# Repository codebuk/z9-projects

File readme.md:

- Note re projhect UUIDs

stored in [project name].kicad_pro

snup ####################
  "sheets": [
    [
      "8d063f79-9282-4820-bcf4-1ff3c006cf08",
      "Root"
    ],

then 'root' schmeatic 
snip ############
(kicad_sch
	(version 20250114)
	(generator "eeschema")
	(generator_version "9.0")
	(uuid "8d063f79-9282-4820-bcf4-1ff3c006cf08")
	(paper "A3")
	(title_block
		(date "2024-05-30")
	)

-- project uuids
old pdm 8d063f79-9282-4820-bcf4-1ff3c006cf08
new pdm b643db5c-578e-4b48-aafc-cc4190db582a

shared 

new 0d832c56-2071-4d02-b574-dc412c8c5a75

8d063f79-9282-4820-bcf4-1ff3c006cf08

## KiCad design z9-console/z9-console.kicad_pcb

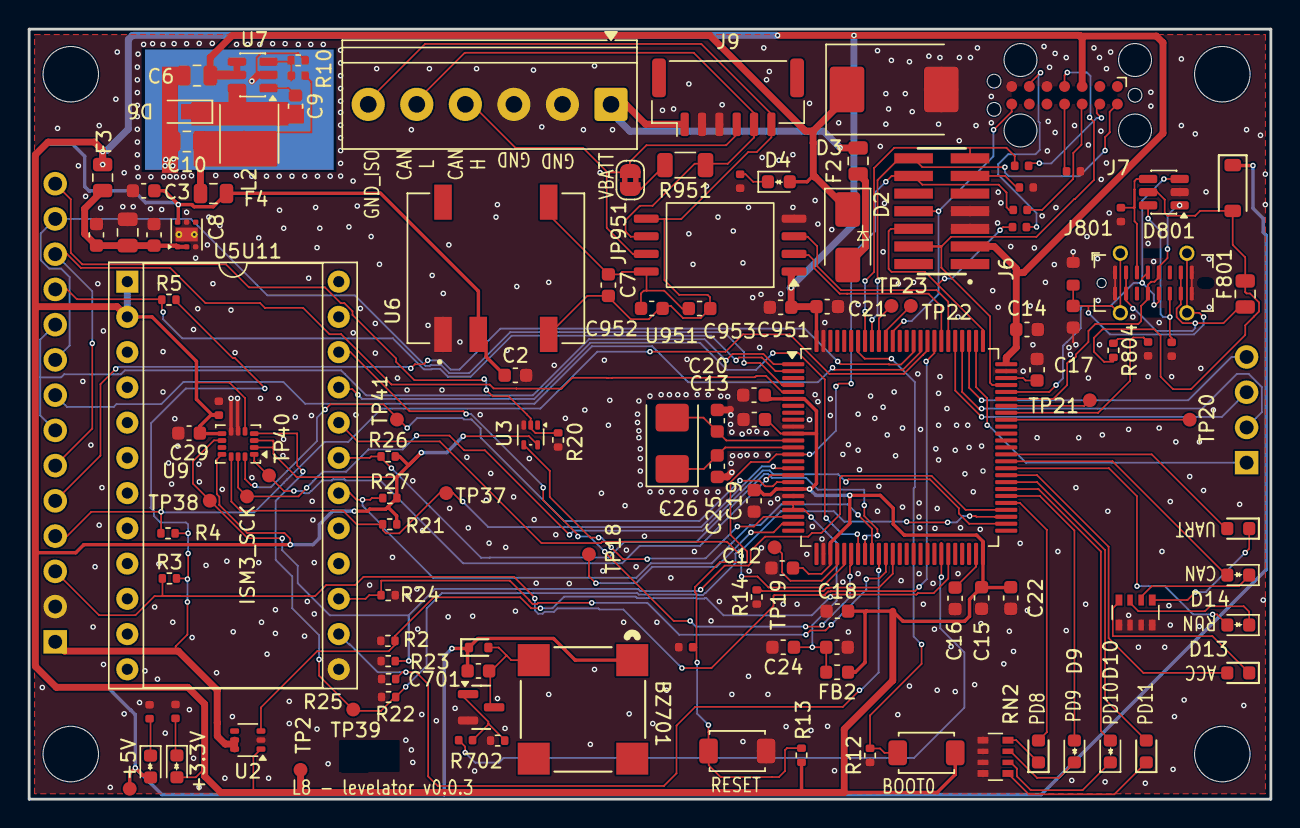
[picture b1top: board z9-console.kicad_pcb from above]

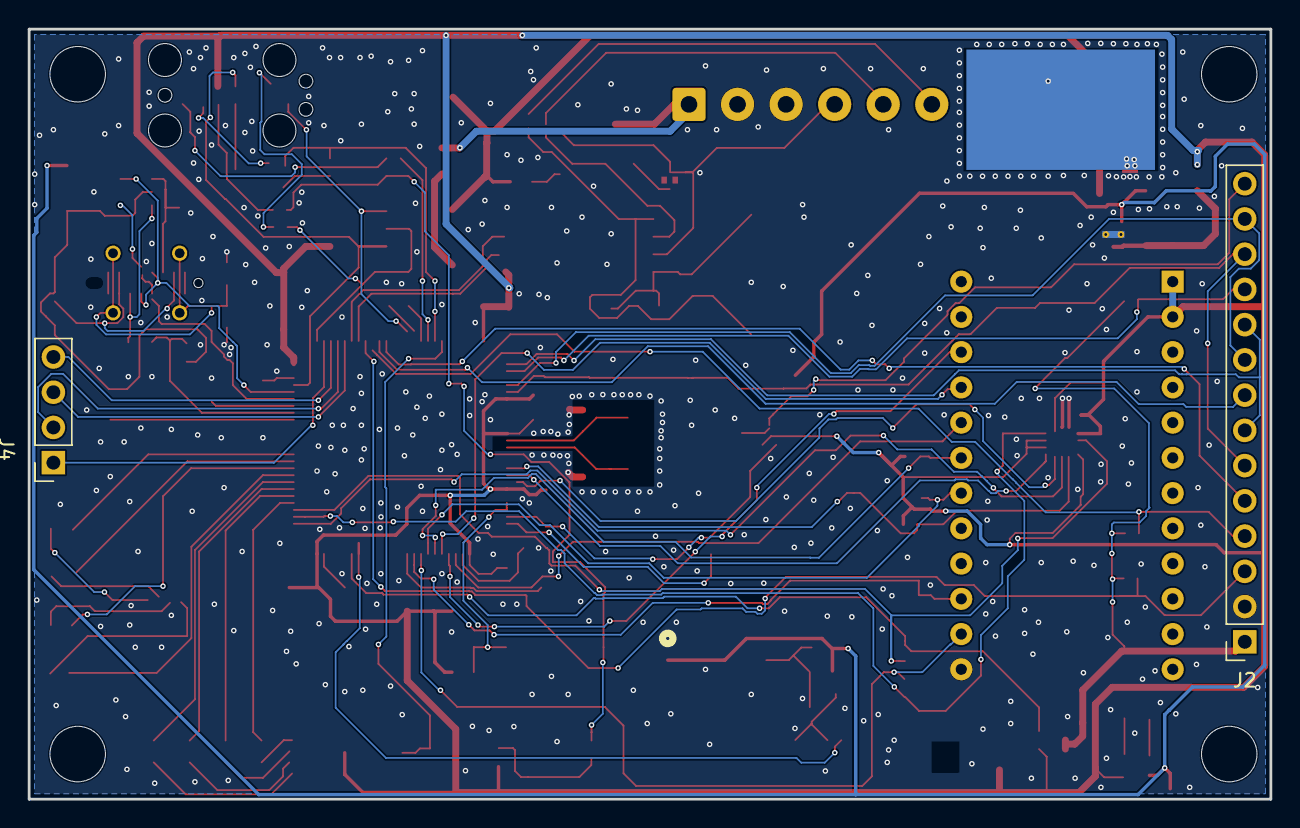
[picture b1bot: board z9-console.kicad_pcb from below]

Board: 2 copper layers, 89.5 x 55.5 mm, 130 parts (2 on the bottom side), 101 nets.

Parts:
BZ701: Buzzer_-_MLT-8530; Buzzer - MLT-8530_JHE
C2, C3, C7, C22, C29, C952: 10uF; C_0603_1608Metric
C4, C23: 1uF; C_0603_1608Metric
C5, C10: 22uF; C_0805_2012Metric
C6: 10uF; C_0805_2012Metric
C8, C9, C12, C13, C14, C15, C18, C19, C20, C21, C24, C701, C951, C953: 100nF; C_0603_1608Metric
C11: 10nF; C_0402
C16, C17: 2.2uF; C_0603_1608Metric
C25, C26: 18pF; C_0603_1608Metric
C28: 100nF; C_0402
C801: 47nF; C_0603
D2: SS54; D_SMA - polarity
D3: SM15T100CA; D_SMC
D4, D5, D7, D10, D14: LED-RED; LED_0603_1608Metric - polarity
D6: V1P6-M3/H 60V 1A; D_MicroSMP_AK
D8, D11, D12, D15: LED-YELLOW; D_0603
D9, D13: LED-WHITE; LED_0603_1608Metric - polarity
D701: RB751S-40; D_SOD-523
D801: SRV05-4; SOT-23-6
D802: B5819W SL; D_SOD-123
F2, F3, F4, F801: Fuse; Fuse_0805_2012Metric
FB2: 4.7uH; L_0603_1608Metric
H901, H902, H903, H904: MountingHole; MountingHole_4mm
J2: LCD 3.2" 240x320 Conn_01x14_Pin; PinSocket_1x14_P2.54mm_Vertical
J4: Conn_01x04_Pin; PinSocket_1x04_P2.54mm_Vertical
J6: ST_STDC14 - SAMTEC_FTSH-107-01-F-DV-K-Fix; Conn_SAMTEC_FTSH-107-01-F-DV-K-Fix
J7: TC2070 - TAG Connect; Tag-Connect_TC2070-IDC-FP_2x07_P1.27mm_Vertical
J9: JST GH; JST_GH_BM06B-GHS-TBT_1x06-1MP_P1.25mm_Vertical
J10: Screw_Terminal_01x06; TerminalBlock_Phoenix_PT-1,5-6-3.5-H_1x06_P3.50mm_Horizontal
J801: USB_C_Receptacle_USB2.0_16P; USB_C_Receptacle_G-Switch_GT-USB-7051x
JP951: SolderJumper_2_Bridged; SolderJumper-2_P1.3mm_Bridged2Bar_RoundedPad1.0x1.5mm
L2: 3.3uH; L_Sunlord_SWPA4030S
Q701: AO3400A; Q_SOT-23
R2, R3, R4, R5, R10, R12, R13, R14, R20, R21, R22, R23, R24, R25, R26, R27, R702, R804: 10K; R_0402_1005Metric
R7, R8, R11: 2.2K; R_0402
R9: 56K; R_0402
R15, R16, R17, R18, R19, R701: 100R; R_0402
R801: 1MΩ; R_0603
R802, R803: 5.1kΩ; R_0402
R805: 2.2k; R_0402
R951: 120R; R_1206_3216Metric
RN2, RN3: 1k; R_Array_Convex_4x0603
SW2, SW3: SW_Push; SW_TS-1088-AR02016
TP2: +3.3V; TestPoint_Pad_D1.0mm FP .6R
TP3: 5V; TestPoint_Pad_D1.0mm FP .6R
TP18: PA1; TestPoint_Pad_D1.0mm FP .6R
TP19: PA4; TestPoint_Pad_D1.0mm FP .6R
TP20: PA8; TestPoint_Pad_D1.0mm FP .6R
TP21: PA10; TestPoint_Pad_D1.0mm FP .6R
TP22: PB4; TestPoint_Pad_D1.0mm FP .6R
TP23: PB5; TestPoint_Pad_D1.0mm FP .6R
TP37: ISM_CS; TestPoint_Pad_D1.0mm FP .6R
TP38: ISM_INT1; TestPoint_Pad_D1.0mm FP .6R
TP39: ISM_INT2; TestPoint_Pad_D1.0mm FP .6R
TP40: ISM_SDO; TestPoint_Pad_D1.0mm FP .6R
TP41: ISM_SDI; TestPoint_Pad_D1.0mm FP .6R
TP42: ISM3_SCK; TestPoint_Pad_D1.0mm FP .6R
U2: TPS22919DCKR; SOT-363_SC-70-6
U3: SN74LVC1G14DRLR; SOT-553
U5: TLV76733DRVx; WSON-6-1EP_2x2mm_P0.65mm_EP1x1.6mm_ThermalVias
U6: B0505XT-1WR3; B0505_Isolated_SMD
U7: LMR14006YDDCR; SOT-23-6
U8: STM32F427V_G-I_Tx; LQFP-100_14x14mm_P0.5mm
U9: ISM330DHCX; LGA-14_3x2.5mm_P0.5mm_LayoutBorder3x4y
U11: ST_SENSOR_2; DIP-24_W15.24mm_Socket- nox
U951: ISO1042-Q1; SOIC-8_7.5x5.85mm_P1.27mm
X2: 8MHz 20pF; Crystal_SMD_5032-2Pin_5.0x3.2mm

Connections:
+3.3V: C12.2, C13.2, C14.2, C15.2, C18.2, C19.2, C20.2, C21.2, C22.2, C28.1, C29.1, C951.1, D5.2 (A), F3.2, FB2.1, J6.3 (VCC), J7.3 (VCC), R13.1, R21.2, R26.2, R27.2, SW2.2 (B), TP2.1, U2.1 (VIN), U3.5 (VCC), U8.6 (VBAT), U8.11 (VDD), U8.19 (VDD), U8.28 (VDD), U8.50 (VDD), U8.75 (VDD), U8.100 (VDD), U9.2 (SDx), U9.3 (SCx), U9.5 (VDDIO), U9.8 (VDD), U9.11 (SDO_AUX), U11.1 (VDD), U11.2 (VDD_IO), U951.1 (VCC1)
+5V: BZ701.1 (+), C2.1, C3.1, C701.1, D7.2 (A), D701.1, D802.1, F4.2, TP3.1, U5.6 (IN), U6.2 (+VIN)
/+5V_ISO: C7.1, C952.1, C953.1, U6.5 (+VOUT), U951.8 (VCC2)
/CAN1_RX: U8.81 (PD0), U951.3 (RXD)
/CAN1_TX: U8.82 (PD1), U951.2 (TXD)
/CAN_H: J9.4, J10.4, JP951.2 (B), U951.7 (CANH)
/CAN_L: J9.5, J10.5, R951.1, U951.6 (CANL)
/GND_ISO: C7.2, C952.2, C953.2, J9.6, J10.6, U6.4 (-VOUT), U951.5 (GND2)
/LCD_DC: J2.5 (D/C), U8.86 (PD5)
/LCD_LED: J2.8 (LED), U8.85 (PD4)
/LCD_ON: R2.2, U2.3 (ON), U8.45 (PE14)
/LCD_RESET: J2.4 (RESET), R4.1, U8.84 (PD3)
/MCU/BOOT0: R12.2, SW2.1 (A), U8.94 (BOOT0)
/MCU/BOOT1: R14.2, U8.37 (PB2)
/MCU/NRST: C11.2, J6.12 (~RST), R13.2, R17.1, SW3.2 (B), U8.14 (NRST)
/MCU/PA1: TP18.1, U8.24 (PA1)
/MCU/PA4: TP19.1, U8.29 (PA4)
/MCU/PA8: TP20.1, U8.67 (PA8)
/MCU/PB4: TP22.1, U8.90 (PB4)
/MCU/PB5: TP23.1, U8.91 (PB5)
/MCU/PD8: D8.2, U8.55 (PD8)
/MCU/PD9: D9.2 (A), U8.56 (PD9)
/MCU/PD10: D10.2 (A), U8.57 (PD10)
/MCU/PD11: D11.2, U8.58 (PD11)
/MCU/PD12: D12.2, U8.59 (PD12)
/MCU/PD13: D13.2 (A), U8.60 (PD13)
/MCU/PD14: D14.2 (A), U8.61 (PD14)
/MCU/PD15: D15.2, U8.62 (PD15)
/MCU/RCC_OSC_IN: C25.1, U8.12 (PH0), X2.2
/MCU/RCC_OSC_OUT: C26.1, U8.13 (PH1), X2.1
/MCU/SYS_JTCK-SWCLK: J6.6 (JCLK/SWCLK), R18.1, U8.76 (PA14)
/MCU/SYS_JTDO-SWO: J6.8 (JTDO/SWO), J7.8 (JTDO/SWO), U8.89 (PB3)
/MCU/SYS_JTMS-SWDIO: J6.4 (JTMS/SWDIO), J7.4 (JTMS/SWDIO), U8.72 (PA13)
/MCU/USART1_RX: J6.13 (VCP_RX), R19.1, U8.93 (PB7)
/MCU/USART1_TX: J6.14 (VCP_TX), J7.14 (VCP_TX), U8.92 (PB6)
/PE13: R701.2, U8.44 (TIM1_CH3)
/SPI1_CS: R26.1, U8.33 (PC4), U11.19 (CS)
/SPI1_CS2: R27.1, U8.34 (PC5), U11.18 (SPI_dut_CS2)
/SPI1_IRQ: R25.2, U8.35 (PB0), U11.14 (DIL_INT1)
/SPI1_IRQ2: R24.2, U8.36 (PB1), U11.15 (DIL_INT2)
/SPI1_SCK: U8.30 (PA5), U11.20 (SCL)
/SPI1_SDI: U8.31 (PA6), U11.22 (SDO)
/SPI1_SDO: U8.32 (PA7), U11.21 (SDA)
/SPI2_CS: R21.1, TP37.1, U8.16 (PC1), U9.12 (CS)
/SPI2_IRQ: R22.2, TP39.1, U8.53 (PB14), U9.4 (INT1)
/SPI2_IRQ2: R23.2, TP38.1, U8.54 (PB15), U9.9 (INT2)
/SPI2_SCK: TP42.1, U8.52 (PB13), U9.13 (SCL)
/SPI2_SDI: TP40.1, U8.17 (PC2), U9.1 (SDO/SA0)
/SPI2_SDO: TP41.1, U8.18 (PC3), U9.14 (SDA)
/SPI3_CS: J4.1, U8.77 (PA15)
/SPI3_SCK: J4.4, U8.78 (PC10)
/SPI3_SDI: J4.2, U8.79 (PC11)
/SPI3_SDO: J4.3, U8.80 (PC12)
/SPI4_CS_1: J2.11 (T_CS), R5.1, U8.2 (PE3)
/SPI4_CS_2: J2.3 (CS), R3.1, U8.83 (PD2)
/SPI4_SCK: J2.7 (SCK), J2.10 (T_SCK), U8.1 (PE2)
/SPI4_SDI: J2.9 (SDO), J2.13 (T_SDO), U8.4 (PE5)
/SPI4_SDO: J2.6 (SDI), J2.12 (T_SDI), U8.5 (PE6)
/SYS_WAKEUP: U3.4, U8.23 (PA0)
/USB_OTG_FS_DM: D801.1, J801.A7 (D-), J801.B7 (D-), U8.70 (PA11)
/USB_OTG_FS_DP: D801.3, J801.A6 (D+), J801.B6 (D+), U8.71 (PA12)
/USB_OTG_FS_VBUS: R804.1, R805.2, U8.68 (PA9)
/VBATT: F2.1, J9.1, J10.1
GND: C2.2, C3.2, C4.1, C5.2, C6.2, C8.2, C10.2, C11.1, C12.1, C13.1, C14.1, C15.1, C16.2, C17.2, C18.1, C19.1, C20.1, C21.1, C22.1, C23.1, C24.2, C25.2, C26.2, C28.2, C29.2, C801.2, C951.2, D3.2 (A2), D6.2 (A), D801.2, J2.2 (GND), J6.5 (GND), J6.7 (GND), J7.5 (GND), J7.7 (GND), J9.2, J9.3, J10.2, J10.3, J801.A1 (GND), J801.A12 (GND), J801.B1 (GND), J801.B12 (GND), Q701.2 (S), R2.1, R7.1, R8.1, R10.1, R11.1, R12.1, R14.1, R15.2, R16.2, R20.1, R22.1, R23.1, R24.1, R25.1, R702.1, R801.2, R802.1, R803.1, R805.1, RN2.5 (R4.2), RN2.6 (R3.2), RN2.7 (R2.2), RN2.8 (R1.2), RN3.5 (R4.2), RN3.6 (R3.2), RN3.7 (R2.2), RN3.8 (R1.2), SW3.1 (A), U2.2 (GND), U3.3 (GND), U5.3 (GND), U5.5 (GND), U5.7 (PAD), U6.1 (-VIN), U7.2 (GND), U8.10 (VSS), U8.20 (VSSA), U8.27 (VSS), U8.74 (VSS), U8.99 (VSS), U9.6 (GND), U9.7 (GND), U11.13 (GND), U951.4 (GND1)
unnamed: BZ701.2 (-), C701.2, D701.2, Q701.3 (D)
unnamed: C10.1, F4.1, L2.2, R9.1
unnamed: D2.2 (A), F2.2
unnamed: C6.1, D2.1 (K), D3.1 (A1), D4.2 (A), U7.4 (~SHDN), U7.5 (VIN)
unnamed: D4.1 (K), R7.2
unnamed: D5.1 (K), R8.2
unnamed: C9.2, D6.1 (K), L2.1, U7.6 (SW)
unnamed: D7.1 (K), R11.2
unnamed: D9.1 (K), RN2.3 (R3.1)
unnamed: D10.1 (K), RN2.2 (R2.1)
unnamed: D13.1 (K), RN3.3 (R3.1)
unnamed: D14.1 (K), RN3.2 (R2.1)
unnamed: D801.5, D802.2, F801.2, R804.2
unnamed: F801.1, J801.A4 (VBUS), J801.A9 (VBUS), J801.B4 (VBUS), J801.B9 (VBUS)
unnamed: J2.14 (T_IRQ), R20.2, U3.2
unnamed: J2.1 (VCC), R3.2, R4.2, R5.2, U2.5 (QOD), U2.6 (VOUT)
unnamed: J6.11 (GNDDetect), R15.1
unnamed: J7.11 (GNDDetect), R16.1
unnamed: J7.6 (JCLK/SWCLK), R18.2
unnamed: J7.13 (VCP_RX), R19.2
unnamed: J7.12 (~RST), R17.2
unnamed: D801.4, J801.A5 (CC1), R803.2
unnamed: D801.6, J801.B5 (CC2), R802.2
unnamed: C801.1, J801.S1 (SHIELD), R801.1
unnamed: JP951.1 (A), R951.2
unnamed: Q701.1 (G), R701.1, R702.2
unnamed: D11.1, RN2.1 (R1.1)
unnamed: D8.1, RN2.4 (R4.1)
unnamed: D15.1, RN3.1 (R1.1)
unnamed: D12.1, RN3.4 (R4.1)
unnamed: C4.2, C5.1, C8.1, F3.1, U5.1 (OUT), U5.2 (SNS)
unnamed: C9.1, U7.1 (CB)
unnamed: R9.2, R10.2, U7.3 (FB)
unnamed: TP21.1, U8.69 (PA10)
unnamed: C16.1, U8.49 (VCAP_1)
unnamed: C17.1, U8.73 (VCAP_2)
unnamed: C23.2, C24.1, FB2.2, U8.21 (VREF+), U8.22 (VDDA)

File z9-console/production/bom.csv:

Designator,Footprint,Quantity,Value,LCSC Part #
BZ701,Buzzer - MLT-8530_JHE,1,Buzzer_-_MLT-8530,C94599
"C10, C5",0805,2,22uF, C45783
C11,C_0402,1,10nF,C15195
"C12, C13, C14, C15, C18, C19, C20, C21, C24, C701, C8, C9, C951, C953",0603,14,100nF,C14663
"C16, C17",0603,2,2.2uF,C23630
"C2, C22, C29, C3, C7, C952",0603,6,10uF,C96446
"C23, C4",0603,2,1uF,C15849
"C25, C26",0603,2,18pF,C1647
C28,C_0402,1,100nF,C1525
C6,0805,1,10uF,C440198
C801,C_0603,1,47nF,C1622
"D10, D14, D4, D5, D7",0603,5,LED-RED,C2286
"D11, D12, D15, D8",D_0603,4,LED-YELLOW,C89811
"D13, D9",0603,2,LED-WHITE,C2290
D2,D_SMA - polarity,1,SS54,C22452
D3,D_SMC,1,SM15T100CA,C1975873
D6,D_MicroSMP_AK,1,V1P6-M3/H 60V 1A,C3757499
D701,D_SOD-523,1,RB751S-40,C7502700
D801,SOT-23-6,1,SRV05-4,C2836319
D802,D_SOD-123,1,B5819W SL,C8598
"F2, F3, F4, F801",0805,4,Fuse,C2833485
FB2,0603,1,4.7uH,C1034
J10,"TerminalBlock_Phoenix_PT-1,5-6-3.5-H_1x06_P3.50mm_Horizontal",1,Screw_Terminal_01x06,C5290323
J4,PinSocket_1x04_P2.54mm_Vertical,1,Conn_01x04_Pin,C7500773
J6,Conn_SAMTEC_FTSH-107-01-F-DV-K-Fix,1,ST_STDC14 - SAMTEC_FTSH-107-01-F-DV-K-Fix,C5307809
J801,USB_C_Receptacle_G-Switch_GT-USB-7051x,1,USB_C_Receptacle_USB2.0_16P,C2843970
J9,JST_GH_BM06B-GHS-TBT_1x06-1MP_P1.25mm_Vertical,1,JST  GH,C189892
L2,L_Sunlord_SWPA4030S,1,3.3uH,C15269
Q701,Q_SOT-23,1,AO3400A,C20917
"R10, R12, R13, R14, R2, R20, R21, R22, R23, R24, R25, R26, R27, R3, R4, R5, R702, R804",0402,18,10K,C25744
"R11, R7, R8, R805",R_0402,4,2.2K,C25879
"R15, R16, R17, R18, R19, R701",R_0402,6,100R,C25076
R801,R_0603,1,1MΩ,C22935
"R802, R803",R_0402,2,5.1kΩ,C25905
R9,R_0402,1,56K,C25796
R951,1206,1,120R,C17909
"RN2, RN3",R_Array_Convex_4x0603,2,1k,C20197
"SW2, SW3",SW_TS-1088-AR02016,2,SW_Push,C720477
U2,SOT-363_SC-70-6,1,TPS22919DCKR,C2149796
U3,SOT-553,1,SN74LVC1G14DRLR,C2877550
U5,WSON-6-1EP_2x2mm_P0.65mm_EP1x1.6mm_ThermalVias,1,TLV76733DRVx,C2848334
U6,B0505_Isolated_SMD,1,B0505XT-1WR3,C19188495
U7,SOT-23-6,1,LMR14006YDDCR,C477919
U8,LQFP-100_14x14mm_P0.5mm,1,STM32F427V_G-I_Tx,C117815
U9,LGA-14_3x2.5mm_P0.5mm_LayoutBorder3x4y,1,ISM330DHCX, C2655101
U951,SOIC-8_7.5x5.85mm_P1.27mm,1,ISO1042-Q1,C2672259
X2,Crystal_SMD_5032-2Pin_5.0x3.2mm,1,8MHz 20pF,C115962

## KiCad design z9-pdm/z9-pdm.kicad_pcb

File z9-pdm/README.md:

# l8-console-pcb

sys_wakup needs  solution for low poer

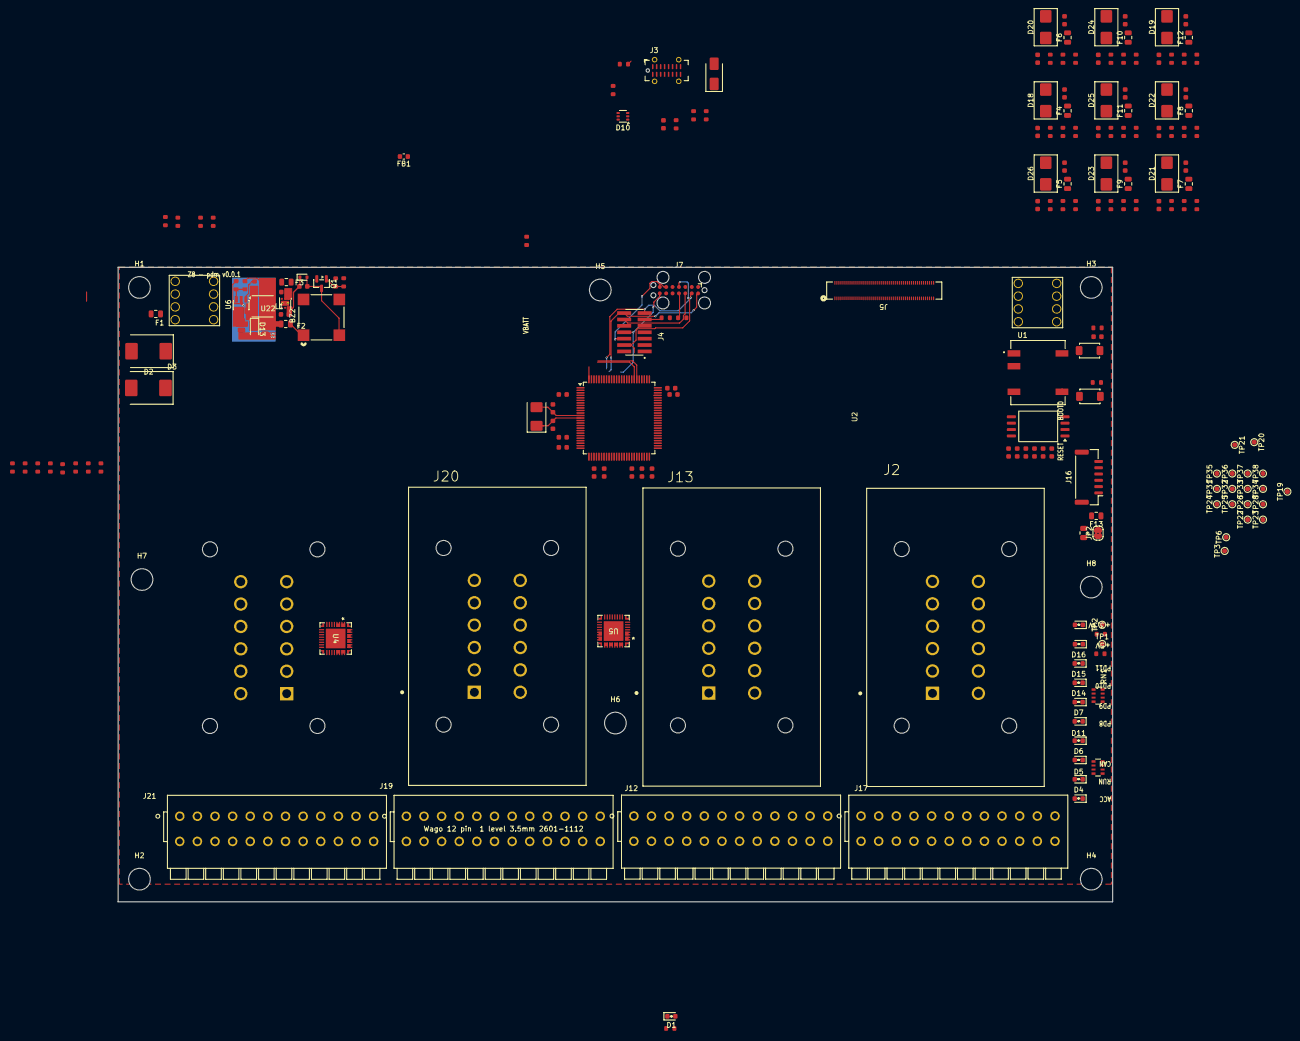
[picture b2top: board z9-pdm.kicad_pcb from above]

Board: 4 copper layers, 197.5 x 126.0 mm, 201 parts (1 on the bottom side), 165 nets.

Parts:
BZ2: Buzzer_-_MLT-8530; Buzzer - MLT-8530_JHE
C1, C8: 2.2uF; C_0603
C2, C9, C11, C12, C15, C16, C17, C18, C22, C25, C30, C46: 100nF; C_0603
C3: 10uF; C_0805
C7, C21, C24, C26, C27, C28: 10uF; C_0603
C13, C14: 18pF; C_0603
C19: 22uF; C_0805
C20, C31, C33, C35, C37, C39, C41, C43, C45, C47: 10nF; C_0603
C23: 1uF; C_0603
C29, C32, C34, C36, C38, C40, C42, C44, C48: 1nF; C_0603
D1, D6, D8, D9, D15: LED-RED; LED_0603_1608Metric - polarity
D2: B340; D_SMC
D3: SM15T100CA; D_SMC
D4, D7, D11, D16: LED-YELLOW; LED_0603_1608Metric - polarity
D5, D14: LED-WHITE; LED_0603_1608Metric - polarity
D10: NUP4202; SOT-363_SC-70-6
D12: RB751S-40; D_SOD-523
D13: Diode - Schotty V1P6-M3/H 60V 1A; D_MicroSMP_AK
D17: SS14; D_SMA
D18, D19, D20, D21, D22, D23, D24, D25, D26: SMBJ24CA; D_SMB_TVS
F1, F2, F3, F4, F5, F6, F7, F8, F9, F10, F11, F12, F13: Fuse_16V_500mA_100A_1A_150mΩ_0805_PTC_Resettable_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; Fuse_0805_2012Metric
FB1: 4.7uH; L_0603_1608Metric
H1, H2, H3, H4, H5, H6, H7, H8: MountingHole_-_4MM; MountingHole_4.3mm_M4_DIN965
J2, J13, J20, J22: TE_DT15-12PC-B016 -Conn_01x12; TE_DT15-12PC-B016
J3: USB_C_Receptacle_USB2.0_16P-GT-USB-7051A; USB_C_Receptacle_G-Switch_GT-USB-7051x
J4: Conn_ST_STDC14; SAMTEC_FTSH-107-01-F-DV-K-Fix
J5: DF40HC3.0-100DS-0.4V51; CONN_DF40HC-100DS_HIR
J7: Conn_TagConnect_2070; Tag-Connect_TC2070-IDC-FP_2x07_P1.27mm_Vertical
J10, J11: RedCubeTerminal; M6_Hole_8Pin_7461084
J12, J17, J19, J21: Wago 12 pin 1 level 3.5mm 2601-1112; WAGO 2601-1112
J16: JST GH; JST_GH_BM06B-GHS-TBT_1x06-1MP_P1.25mm_Vertical
JP2: SolderJumper_2_Bridged; SolderJumper-2_P1.3mm_Bridged2Bar_RoundedPad1.0x1.5mm
L1: 3.3uH; L_Sunlord_SWPA4030S
Q1: AO3400A; SOT-23
R1: 120R; R_0805_2012Metric
R2, R3, R7, R11, R12, R14, R15, R22, R23: 2.7kΩ; R_0603
R4, R17, R20, R21: 2.2kΩ; R_0603
R5, R54: 5.1kΩ; R_0603
R6, R8, R25, R28, R31, R35, R38, R41, R46, R49, R52, R60: 100Ω; R_0603
R9, R16, R18, R27, R30, R36, R37, R40, R43, R44, R45, R48, R51, R58, R62: 10kΩ; R_0603
R13, R24: 47Ω; R_0603
R19: 56kΩ; R_0603
R26, R29, R34, R39, R42, R47, R50, R53, R61: 47kΩ; R_0603
R59: 1MΩ; R_0603
R223: 200Ω; R_0603
RN1, RN2: 1k; R_Array_Convex_4x0603
SW1, SW2: Tactile Button, 160gf; SW_TS-1088-AR02016
TP1, TP2, TP3, TP6, TP19, TP20, TP21, TP22, TP23, TP24, TP25, TP26, TP28, TP31, TP32, TP33, TP34, TP35, TP36, TP37, TP38: PE0; TestPoint_Pad_D1.0mm
U1: B0505XT-1WR3; B0505_Isolated_SMD
U2: ISO1042-Q1; SOIC-8_7.5x5.85mm_P1.27mm
U3: STM32F427V_G-I_Tx; LQFP-100_14x14mm_P0.5mm
U4, U5: VN9E30F; QFN6x6_VN9D30_STM-cleanimport
U6: LMR14206; SOT-23-6
U22: TLV76733DRVx; WSON-6-1EP_2x2mm_P0.65mm_EP1x1.6mm_ThermalVias
X1: 8MHz 20pF; Crystal_SMD_5032-2Pin_5.0x3.2mm

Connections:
+3.3V: C22.1, U2.1 (VCC1), U4.16 (VDD), U5.16 (VDD)
+3.3VP: C9.1, C11.2, C12.2, C15.2, C16.2, C17.2, C23.2, C26.2, C30.2, D9.2 (A), F3.2, FB1.1, FB1.2, J4.3 (VCC), J5.26, J7.3 (VCC), R43.1, SW1.2 (B), TP2.1, U3.6 (VBAT), U3.11 (VDD), U3.19 (VDD), U3.21 (VREF+), U3.22 (VDDA), U3.28 (VDD), U3.50 (VDD), U3.75 (VDD), U3.100 (VDD)
+5V: BZ2.1 (+), C2.1, C21.1, C27.1, D8.2 (A), D12.1, D17.1, F2.2, TP1.1, U1.2 (+VIN), U22.6 (IN)
+12V: C3.1, D1.2 (A), D2.1 (K), D3.1 (A1), U4.33 (VCC), U5.33 (VCC), U6.4 (~SHDN), U6.5 (VIN)
+BATT: F1.1, J2.1, J2.2, J10.1, J17.1 (1_1), J17.2 (1_2), J17.3 (2_1), J17.4 (2_2)
/+5V_ISO: C24.1, C25.1, C28.1, U1.5 (+VOUT), U2.8 (VCC2)
/ADC1_IN1: C47.1, R61.1, R62.2, U3.24 (PA1)
/ADC1_IN2: C31.1, R26.1, R27.2, U3.25 (PA2)
/ADC1_IN3: C33.1, R29.1, R30.2, U3.26 (PA3)
/ADC1_IN4: C35.1, R34.1, R37.2, U3.29 (PA4)
/ADC1_IN6: C37.1, R39.1, R40.2, U3.31 (PA6)
/ADC1_IN7: C39.1, R42.1, R44.2, U3.32 (PA7)
/ADC1_IN8: C41.1, R47.1, R48.2, U3.35 (PB0)
/ADC1_IN10: C43.1, R50.1, R51.2, U3.15 (PC0)
/ADC1_IN15: C45.1, R53.1, R58.2, U3.34 (PC5)
/CAN1_RX: U2.3 (RXD), U3.81 (PD0)
/CAN1_TX: U2.2 (TXD), U3.82 (PD1)
/CAN_H: J2.4, J16.4, J17.7 (4_1), J17.8 (4_2), JP2.2 (B), U2.7 (CANH)
/CAN_L: J2.5, J16.5, J17.9 (5_1), J17.10 (5_2), R1.1, U2.6 (CANL)
/GND_ISO: C24.2, C25.2, C28.2, U1.4 (-VOUT), U2.5 (GND2)
/HC_1: J19.21 (11_1), J19.22 (11_2), J20.6, J21.1 (1_1), J21.2 (1_2), J22.1, U4.4 (OUTPUT0), U5.22 (OUTPUT5)
/HC_2: J21.5 (3_1), J21.6 (3_2), J22.2, U4.32 (OUTPUT1)
/HC_3: J21.9 (5_1), J21.10 (5_2), J22.3, U4.30 (OUTPUT2)
/HC_4: J21.13 (7_1), J21.14 (7_2), J22.4, U4.28 (OUTPUT3)
/HC_5: J21.17 (9_1), J21.18 (9_2), J22.5, U4.26 (OUTPUT4)
/HC_6: J21.21 (11_1), J21.22 (11_2), J22.6, U4.22 (OUTPUT5)
/HC_7: J19.1 (1_1), J19.2 (1_2), J20.1, U5.4 (OUTPUT0)
/HC_8: J19.5 (3_1), J19.6 (3_2), J20.2, U5.32 (OUTPUT1)
/HC_9: J19.9 (5_1), J19.10 (5_2), J20.3, U5.30 (OUTPUT2)
/HC_10: J19.13 (7_1), J19.14 (7_2), J20.4, U5.28 (OUTPUT3)
/HC_11: J19.17 (9_1), J19.18 (9_2), J20.5, U5.26 (OUTPUT4)
/MCU/BOOT0: R45.2, SW1.1 (A), U3.94 (BOOT0)
/MCU/BOOT1: J5.20, R36.2, U3.37 (PB2)
/MCU/NRST: C20.2, J4.12 (~RST), J7.12 (~RST), R43.2, SW2.1 (A), U3.14 (NRST)
/MCU/PA8: J5.19, TP19.1, U3.67 (PA8)
/MCU/PA10: TP6.1, U3.69 (PA10)
/MCU/PB1: TP3.1, U3.36 (PB1)
/MCU/PB4: J5.22, TP20.1, U3.90 (PB4)
/MCU/PB5: J5.21, TP21.1, U3.91 (PB5)
/MCU/PB8: J5.25, TP22.1, U3.95 (PB8)
/MCU/PB9: J5.31, TP23.1, U3.96 (PB9)
/MCU/PB10: J5.32, TP24.1, U3.47 (PB10)
/MCU/PB11: J5.33, TP25.1, U3.48 (PB11)
/MCU/PB12: J5.34, TP26.1, U3.51 (PB12)
/MCU/PC7: J5.37, U3.64 (PC7)
/MCU/PC8: J5.38, U3.65 (PC8)
/MCU/PC9: J5.39, U3.66 (PC9)
/MCU/PD7: J5.47, TP28.1, U3.88 (PD7)
/MCU/PD8: D7.2 (A), J5.46, U3.55 (PD8)
/MCU/PD9: D14.2 (A), J5.45, U3.56 (PD9)
/MCU/PD10: D15.2 (A), J5.44, U3.57 (PD10)
/MCU/PD11: D16.2 (A), J5.43, U3.58 (PD11)
/MCU/PD12: D4.2 (A), U3.59 (PD12)
/MCU/PD13: D5.2 (A), U3.60 (PD13)
/MCU/PD14: D6.2 (A), U3.61 (PD14)
/MCU/PD15: D11.2 (A), U3.62 (PD15)
/MCU/PE0: J5.15, TP33.1, U3.97 (PE0)
/MCU/PE1: J5.14, TP34.1, U3.98 (PE1)
/MCU/PE7: J5.13, TP32.1, U3.38 (PE7)
/MCU/PE8: J5.12, TP31.1, U3.39 (PE8)
/MCU/PE9: J5.11, TP35.1, U3.40 (PE9)
/MCU/PE10: J5.10, TP36.1, U3.41 (PE10)
/MCU/PE11: J5.50, TP37.1, U3.42 (PE11)
/MCU/PE12: J5.49, TP38.1, U3.43 (PE12)
/MCU/SYS_JTCK-SWCLK: J4.6 (JCLK/SWCLK), J7.6 (JCLK/SWCLK), U3.76 (PA14)
/MCU/SYS_JTDO-SWO: J4.8 (JTDO/SWO), J7.8 (JTDO/SWO), U3.89 (PB3)
/MCU/SYS_JTMS-SWDIO: J4.4 (JTMS/SWDIO), J7.4 (JTMS/SWDIO), U3.72 (PA13)
/MCU/USART1_RX: J4.13 (VCP_RX), J7.13 (VCP_RX), U3.93 (PB7)
/MCU/USART1_TX: J4.14 (VCP_TX), J7.14 (VCP_TX), U3.92 (PB6)
/SENSE_1: F12.1, J12.1 (1_1), J12.2 (1_2), J13.1
/SENSE_2: F4.1, J12.5 (3_1), J12.6 (3_2), J13.2
/SENSE_3: F5.1, J12.9 (5_1), J12.10 (5_2), J13.3
/SENSE_4: F6.1, J12.13 (7_1), J12.14 (7_2), J13.4
/SENSE_5: F7.1, J12.17 (9_1), J12.18 (9_2), J13.5
/SENSE_6: F8.1, J12.21 (11_1), J12.22 (11_2), J13.6
/SENSE_7: F9.1, J2.9, J17.17 (9_1), J17.18 (9_2)
/SENSE_8: F10.1, J2.10, J17.19 (10_1), J17.20 (10_2)
/SENSE_9: F11.1, J2.11, J17.21 (11_1), J17.22 (11_2)
/TIM1_CH3: R8.2, U3.44 (PE13)
/USB_OTG_FS_DM: D10.1, J3.A7 (D-), J3.B7 (D-), U3.70 (PA11)
/USB_OTG_FS_DP: D10.3, J3.A6 (D+), J3.B6 (D+), U3.71 (PA12)
/USB_OTG_FS_VBUS: R16.2, R17.2, U3.68 (PA9)
/VIPOWER_CS1: R2.1, U3.33 (PC4), U3.77 (PA15)
/VIPOWER_CS2: J5.40, R11.1, U3.7 (PC13)
/VIPOWER_DI0: J5.41, R15.1, U3.8 (PC14)
/VIPOWER_DI1: J5.42, R22.1, U3.9 (PC15)
/VIPOWER_PWM: R14.1, U3.63 (PC6)
/VIPOWER_SCK: R7.1, U3.78 (PC10)
/VIPOWER_SDI: R3.1, U3.79 (PC11)
/VIPOWER_SDO: R223.1, U3.80 (PC12)
/connectors/5V_SENSOR_POWER: J2.8, J17.15 (8_1), J17.16 (8_2)
/connectors/+5V_ISO: J2.7, J17.13 (7_1), J17.14 (7_2)
/connectors/GND_ISO: J2.6, J16.6, J17.11 (6_1), J17.12 (6_2)
/connectors/SENSE_GROUND: J2.12, J12.3 (2_1), J12.4 (2_2), J12.7 (4_1), J12.8 (4_2), J12.11 (6_1), J12.12 (6_2), J12.15 (8_1), J12.16 (8_2), J12.19 (10_1), J12.20 (10_2), J12.23 (12_1), J12.24 (12_2), J13.7, J13.8, J13.9, J13.10, J13.11, J13.12, J17.23 (12_1), J17.24 (12_2)
/vipower/VN9E30F1/CS: R11.2, R23.1
/vipower/VN9E30F/CS: R2.2, R12.1
/vipower/VN9E30F/DI0: R15.2, U4.9 (DI0), U5.9 (DI0)
/vipower/VN9E30F/DI1: R22.2, U4.10 (DI1), U5.10 (DI1)
/vipower/VN9E30F/PWM: R14.2, U4.11 (PWM_CLK), U5.11 (PWM_CLK)
/vipower/VN9E30F/SCK: R7.2, U4.13 (SCK), U5.13 (SCK)
/vipower/VN9E30F/SDI: R3.2, U4.14 (SDI), U5.14 (SDI)
/vipower/VN9E30F/SDO: R13.1, R24.1, R223.2
CAN_POWER: F13.1, J16.1
GND: C1.2, C3.2, C7.2, C8.2, C9.2, C11.1, C12.1, C13.2, C14.2, C15.1, C16.1, C17.1, C19.2, C20.1, C21.2, C22.2, C23.1, C26.1, C27.2, C29.2, C30.1, C31.2, C32.2, C33.2, C34.2, C35.2, C36.2, C37.2, C38.2, C39.2, C40.2, C41.2, C42.2, C43.2, C44.2, C45.2, C46.2, C47.2, C48.2, D3.2 (A2), D10.2, D13.2 (A), J2.3, J3.A1 (GND), J3.A12 (GND), J3.B1 (GND), J3.B12 (GND), J4.5 (GND), J4.7 (GND), J5.28, J7.5 (GND), J7.7 (GND), J11.1, J16.2, J16.3, J17.5 (3_1), J17.6 (3_2), J19.3 (2_1), J19.4 (2_2), J19.7 (4_1), J19.8 (4_2), J19.11 (6_1), J19.12 (6_2), J19.15 (8_1), J19.16 (8_2), J19.19 (10_1), J19.20 (10_2), J19.23 (12_1), J19.24 (12_2), J20.7, J20.8, J20.9, J20.10, J20.11, J20.12, J21.3 (2_1), J21.4 (2_2), J21.7 (4_1), J21.8 (4_2), J21.11 (6_1), J21.12 (6_2), J21.15 (8_1), J21.16 (8_2), J21.19 (10_1), J21.20 (10_2), J21.23 (12_1), J21.24 (12_2), J22.7, J22.8, J22.9, J22.10, J22.11, J22.12, Q1.2 (S), R4.1, R5.1, R6.2, R9.1, R17.1, R18.1, R20.1, R21.1, R27.1, R30.1, R35.2, R36.1, R37.1, R40.1, R44.1, R45.1, R48.1, R51.1, R54.1, R58.1, R59.2, R62.1, RN1.1 (R1.1), RN1.2 (R2.1), RN1.3 (R3.1), RN1.4 (R4.1), RN2.1 (R1.1), RN2.2 (R2.1), RN2.3 (R3.1), RN2.4 (R4.1), SW2.2 (B), U1.1 (-VIN), U2.4 (GND1), U3.10 (VSS), U3.20 (VSSA), U3.27 (VSS), U3.74 (VSS), U3.99 (VSS), U4.17 (GND), U5.17 (GND), U6.2 (GND), U22.3 (GND), U22.5 (GND), U22.7 (PAD)
unnamed: BZ2.2 (-), C2.2, D12.2, Q1.3 (D)
unnamed: C19.1, F2.1, L1.2, R19.1
unnamed: C29.1, R25.2, R26.2
unnamed: C32.1, R60.2, R61.2
unnamed: C34.1, R31.2, R34.2
unnamed: C36.1, R38.2, R39.2
unnamed: C38.1, R41.2, R42.2
unnamed: C40.1, R46.2, R47.2
unnamed: C42.1, R49.2, R50.2
unnamed: C44.1, R52.2, R53.2
unnamed: C48.1, R28.2, R29.2
unnamed: D1.1 (K), R4.2
unnamed: D2.2 (A), F1.2, F13.2
unnamed: D4.1 (K), RN2.8 (R1.2)
unnamed: D5.1 (K), RN2.7 (R2.2)
unnamed: D6.1 (K), RN2.6 (R3.2)
unnamed: D7.1 (K), RN1.8 (R1.2)
unnamed: D8.1 (K), R20.2
unnamed: D9.1 (K), R21.2
unnamed: D10.5, D17.2, J3.A4 (VBUS), J3.A9 (VBUS), J3.B4 (VBUS), J3.B9 (VBUS), R16.1
unnamed: D11.1 (K), RN2.5 (R4.2)
unnamed: C18.2, D13.1 (K), L1.1, U6.6 (SW)
unnamed: D14.1 (K), RN1.7 (R2.2)
unnamed: D15.1 (K), RN1.6 (R3.2)
unnamed: D16.1 (K), RN1.5 (R4.2)
unnamed: D18.2 (A), R25.1
unnamed: D18.1 (K), F4.2
unnamed: D19.2 (A), R60.1
unnamed: D19.1 (K), F12.2
unnamed: D20.2 (A), R31.1
unnamed: D20.1 (K), F6.2
unnamed: D21.2 (A), R38.1
unnamed: D21.1 (K), F7.2
unnamed: D22.2 (A), R41.1
unnamed: D22.1 (K), F8.2
unnamed: D23.2 (A), R46.1
unnamed: D23.1 (K), F9.2
unnamed: D24.2 (A), R49.1
unnamed: D24.1 (K), F10.2
unnamed: D25.2 (A), R52.1
unnamed: D25.1 (K), F11.2
unnamed: D26.2 (A), R28.1
unnamed: D26.1 (K), F5.2
unnamed: D10.4, J3.A5 (CC1), R54.2
unnamed: D10.6, J3.B5 (CC2), R5.2
unnamed: C46.1, J3.S1 (SHIELD), R59.1
unnamed: J4.11 (GNDDetect), R35.1
unnamed: J7.11 (GNDDetect), R6.1
unnamed: JP2.1 (A), R1.2
unnamed: Q1.1 (G), R8.1, R9.2
unnamed: C13.1, U3.12 (PH0), X1.2
unnamed: C14.1, U3.13 (PH1), X1.1
unnamed: C8.1, U3.49 (VCAP_1)
unnamed: C1.1, U3.73 (VCAP_2)
unnamed: R12.2, U4.12 (CSN)
unnamed: R13.2, U4.15 (SDO)
unnamed: R23.2, U5.12 (CSN)
unnamed: R24.2, U5.15 (SDO)
unnamed: C18.1, U6.1 (CB)
unnamed: R18.2, R19.2, U6.3 (FB)
unnamed: C7.1, F3.1, U22.1 (OUT), U22.2 (SNS)

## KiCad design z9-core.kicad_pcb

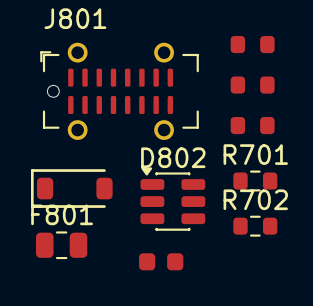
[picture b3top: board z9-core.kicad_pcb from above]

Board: 2 copper layers, 10 parts (0 on the bottom side), 9 nets, no tracks yet.

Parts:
C801: 47nF; C_0603
D801: B5819W SL; D_SOD-123
D802: SRV05-4; SOT-23-6
F801: Fuse; Fuse_0805_2012Metric
J801: USB_C_Receptacle_USB2.0_16P; USB_C_Receptacle_G-Switch_GT-USB-7051x
R701: 2.2K; R_0603_1608Metric
R702: 10K; R_0603_1608Metric
R801: 1MΩ; R_0603
R802: 5.1kΩ; R_0603
R803: 5.1K; R_0603

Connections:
/usbc/USB_OTG_FS_DM: D802.1, J801.A7 (D-), J801.B7 (D-)
/usbc/USB_OTG_FS_DP: D802.3, J801.A6 (D+), J801.B6 (D+)
/usbc/USB_OTG_FS_VBUS: R701.2, R702.1
GND: C801.2, D802.2, J801.A1 (GND), J801.A12 (GND), J801.B1 (GND), J801.B12 (GND), R701.1, R801.2, R802.1, R803.1
unnamed: D801.2, D802.5, F801.2, R702.2
unnamed: F801.1, J801.A4 (VBUS), J801.A9 (VBUS), J801.B4 (VBUS), J801.B9 (VBUS)
unnamed: D802.4, J801.A5 (CC1), R803.2
unnamed: D802.6, J801.B5 (CC2), R802.2
unnamed: C801.1, J801.S1 (SHIELD), R801.1

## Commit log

2025-09-27 init - new repo after conversion to shared
2025-09-27 drc pcb
2025-09-28 fix VP
2025-09-28 pdm sch drc clean
2025-09-28 lcd power switch-- add new accelerometer
2025-09-29 change MEMS device
2025-09-29 cleanup
2025-09-29 remove readme
2025-09-29 cleanup - change fus as test to shorten vale
2025-09-29 remove old files
2025-09-29 annotation issues on shared schematics
2025-09-29 reset shared chematics to correct series
2025-09-29 another reannotate
2025-09-29 update harness to v9
2025-09-29 remove rproject level lib rescue seem to an error
2025-09-29 annotate issues
2025-09-29 found duplicate UUIDs for console and pdm - final changes before renaming z8-pdm
2025-09-29 -- kicad project uuids old pdm 8d063f79-9282-4820-bcf4-1ff3c006cf08 new pdm b643db5c-578e-4b48-aafc-cc4190db582a
2025-09-29 opened pdm - fixed the references
2025-09-29 fix can hl pins
2025-09-29 duplicate uuid fallout - still old l8-kicad references
2025-09-29 drc con - fix ti switch reference - fix stm32 bypass
2025-09-29 drc console complete
2025-09-29 harness clean
2025-09-29 console pcb changes
2025-09-29 remove old l8-kicad references from harness
2025-09-29 cherry pick and harness revest from backup
2025-09-29 fix harness again
2025-09-29 cleanup harness
2025-09-29 console pcb drc - ready for ism fixups
2025-09-29 final lcsc mappings
2025-09-29 white led fix
2025-09-29 remove bogus fields
2025-09-29 populate stdc14
2025-09-30 3d fixes and field removal
2025-09-30 fix stdc - reroute power on pcb
2025-09-30 fix 120R resistor up size to match pdm
2025-09-30 lcsc components and cleanup
2025-09-30 starrted gerbers to jlcpcb - revert to kicad 9.04
2025-09-30 test save in new version will small change
2025-09-30 fix 10uf 25v
2025-09-30 continue lssc fixups
2025-09-30 lcsc changes done - export for prod
2025-09-30 more change - generarte jlc
2025-09-30 more moving offset to library - tedious
2025-09-30 ism issues
2025-09-30 submitted to jlcpcb 00:23 1/10/20025
2025-09-30 add image - start shared ps
2025-09-30 sheet updates

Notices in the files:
parts and their libraries:
Copyright 2016 Accelerated Designs. All rights reserved.
